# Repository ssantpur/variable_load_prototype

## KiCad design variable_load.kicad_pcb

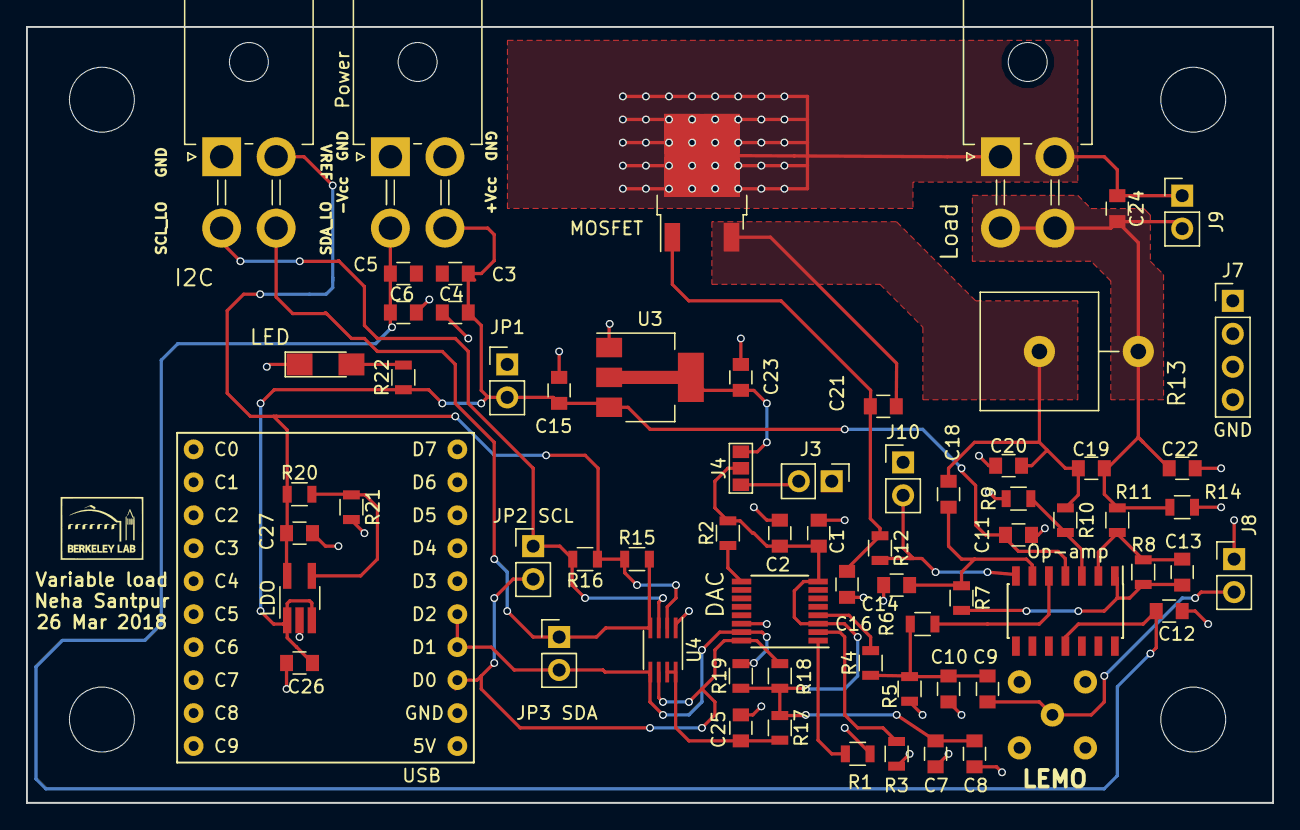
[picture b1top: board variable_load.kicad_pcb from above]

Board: 2 copper layers, 96.0 x 59.8 mm, 69 parts (0 on the bottom side), 30 nets.

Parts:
C1, C2, C3, C4, C5, C6, C7, C8, C9, C10, C11, C12, C13, C14, C15, C16, C18, C19, C20, C21, C22, C23, C24, C25: C; C_0805
C26, C27: 1uF; C_0805
DAC: DAC5578; TSSOP-16_4.4x5mm_Pitch0.65mm
I2C: Conn_01x04; Molex_MiniFit-JR-5569-04A2_2x02x4.20mm_Angled
J3, J8, J9, J10: Conn_01x02; Pin_Header_Straight_1x02_Pitch2.54mm
J4: GS3
J7: GND; Pin_Header_Straight_1x04_Pitch2.54mm
JP1, JP2 SCL, JP3 SDA: Jumper_NO_Small; Pin_Header_Straight_1x02_Pitch2.54mm
LDO: APD123; TSOT-23-5_HandSoldering
LED: LED; LED_1206_HandSoldering
LEMO: LEMO; lemo_epb00250ntn
Load: Conn_01x04; Molex_MiniFit-JR-5569-04A2_2x02x4.20mm_Angled
MOSFET: NTD4858N; TO-252-2
Op-amp: LM324; SOIC-14_3.9x8.7mm_Pitch1.27mm
Power: Conn_01x04; Molex_MiniFit-JR-5569-04A2_2x02x4.20mm_Angled
R1, R2, R3, R4, R5, R6, R7, R12, R14, R15, R16, R18, R19, R20, R21, R22: R; R_0805
R8, R9, R10, R11: 100k; R_0805
R13: R; R_Axial_Power_L25.0mm_W9.0mm_P7.62mm_Vertical
R17: 200k; R_0805
U3: TLV1117-33; SOT-223-3_TabPin2
U4: PCA9306; SSOP-8_2.95x2.8mm_Pitch0.65mm
USB: adafruit_ft232h; adafruit_ft232h_nohole

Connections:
/3V3LDO: C23.1, J4.1, U3.2
/+Vcc: C3.2, C4.2, C11.1, C15.1, C26.1, JP1.2, LDO.1, LDO.3, Op-amp.4, Power.4, R22.1, U3.3
/-Vcc: C5.1, C6.1, C12.1, Op-amp.11, Power.3
/SCL_HI: DAC.16, JP2 SCL.2, R18.2, U4.6, USB.3
/SCL_LO: I2C.3, JP2 SCL.1, R16.2, U4.3
/SDA_HI: DAC.15, JP3 SDA.2, R19.2, U4.5, USB.4, USB.5
/SDA_LO: I2C.4, JP3 SDA.1, R15.2, U4.4
/V1: C9.2, C10.1, R4.1, R5.1, R6.2
/VCC_DAC: C1.1, C2.1, C7.2, C8.2, DAC.3, DAC.8, J4.2, R2.2, R17.1, R18.1, R19.1
/VREF: C27.1, I2C.2, LDO.5, R15.1, R16.1, R20.1, U4.2
GND: C1.2, C2.2, C4.1, C6.2, C7.1, C8.1, C10.2, C11.2, C12.2, C14.2, C15.2, C16.1, C20.2, C22.2, C23.2, C25.1, C26.2, C27.2, DAC.14, I2C.1, J3.1, J7.1, J7.2, J7.3, J7.4, J8.1, J10.1, JP1.1, LDO.2, LED.1, LEMO.2, Power.1, Power.2, R1.2, R3.2, R5.2, R9.1, R14.2, R21.2, U3.1, U4.1, USB.2
unnamed: C9.1, J8.2, LEMO.1
unnamed: C13.1, Op-amp.2, R8.1, R11.2
unnamed: C13.2, Op-amp.1, R7.2, R8.2
unnamed: C14.1, C18.2, Op-amp.6, R7.1
unnamed: C16.2, C21.2, MOSFET.1, R12.1
unnamed: C18.1, C19.1, C20.1, C21.1, MOSFET.3, R10.1, R13.1
unnamed: C19.2, C22.1, C24.2, J9.2, Load.3, Load.4, R11.1, R13.2, R14.1
unnamed: C24.1, J9.1, Load.1, Load.2, MOSFET.2
unnamed: C25.2, R17.2, U4.7, U4.8
unnamed: LED.2, R22.2
unnamed: J3.2, J4.3
unnamed: J10.2, Op-amp.7, R12.2
unnamed: DAC.1, R1.1
unnamed: DAC.9, R2.1
unnamed: DAC.2, R3.1
unnamed: DAC.4, R4.2
unnamed: Op-amp.5, R6.1
unnamed: Op-amp.3, R9.2, R10.2
unnamed: LDO.4, R20.2, R21.1

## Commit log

2018-01-17 Revised
2018-01-23 USB>I2C added
2018-01-23 Add kk_kicad_components.
2018-01-24 level shifter added
2018-01-24 level shifter corrected footprint
2018-03-07 pcb opamps v1
2018-03-07 pcb modified
2018-03-12 pcb v1
2018-03-14 pcb v2
2018-03-16 pcb v3
2018-03-19 pcb v4
2018-03-26 pcb v5
2018-03-26 pcb v6
2018-03-26 pcb v7
2018-03-27 pcb with gerbers
2018-03-27 pcb with gerbers v7
2018-03-30 PCB B MAsk added
